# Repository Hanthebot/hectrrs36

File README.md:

# Hectrrs36

sub 100x100 mm 36 key split keyboard with splay - and TRRS jack!

## Specs
Minor derivated work of ezxzeng's [Hector36 keyboard](https://github.com/ezxzeng/hector36), now with RP2040 zero and TRRS!

## Build guide
WIP, but it should be straightforward.
Maybe checkout uploaded images. 

BOM:
- 2 x PCB (reversible)
- 2 x TRRS socket (PJ320A)
- 2 x RP2040 Zero (no pins required, SMD)
- 36 x MX hotswap socket or variants

In case you are going sandwich cases like me:
- 10 x M2 bolt (length 6 mm)
- 10 x M2 nut (diameter 3 mm)
- 10 x M2 standoff (height 7mm - flexible)
- maybe 8-10 bumpons

Tips:
1. Jump at the back
2. Use 90 degree TRRS jack, and 90 degree usb c cable if possible
    -  due to weird locations of TRRS. It may be fixed in the future

With these being said, it could be the most accessible way to try a splayed keyboard / totem layout!

## License
Following the original work, all the work here is licensed under CC BY-NC-SA 4.0.

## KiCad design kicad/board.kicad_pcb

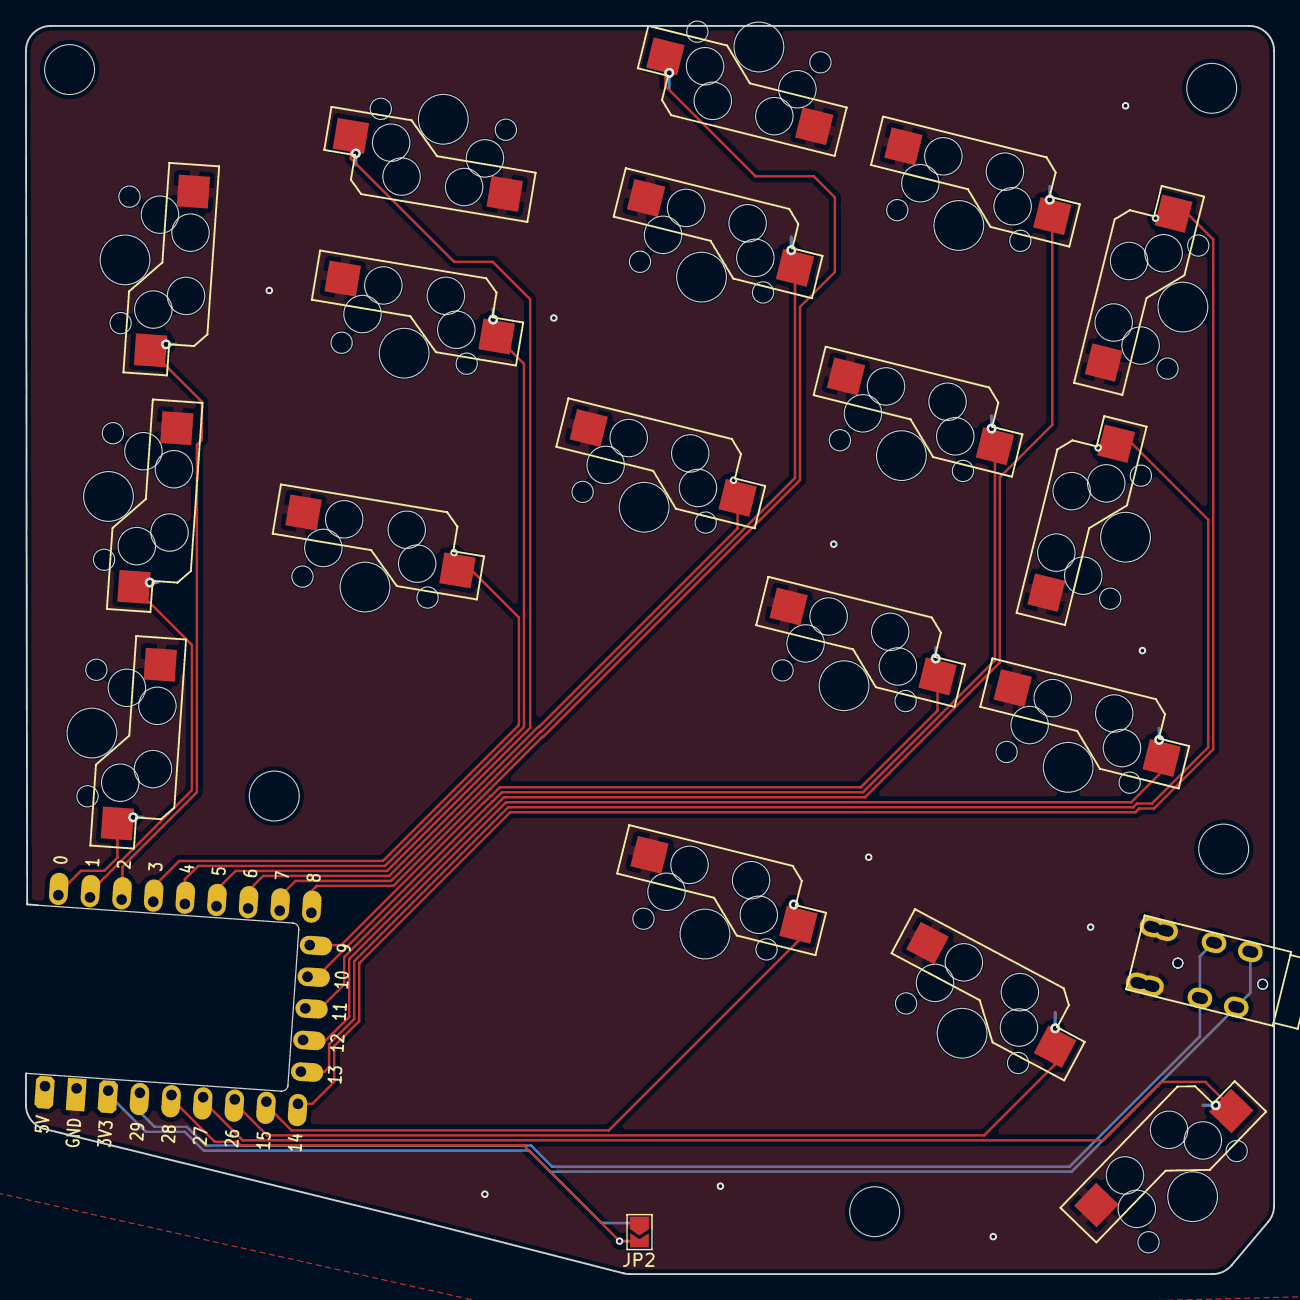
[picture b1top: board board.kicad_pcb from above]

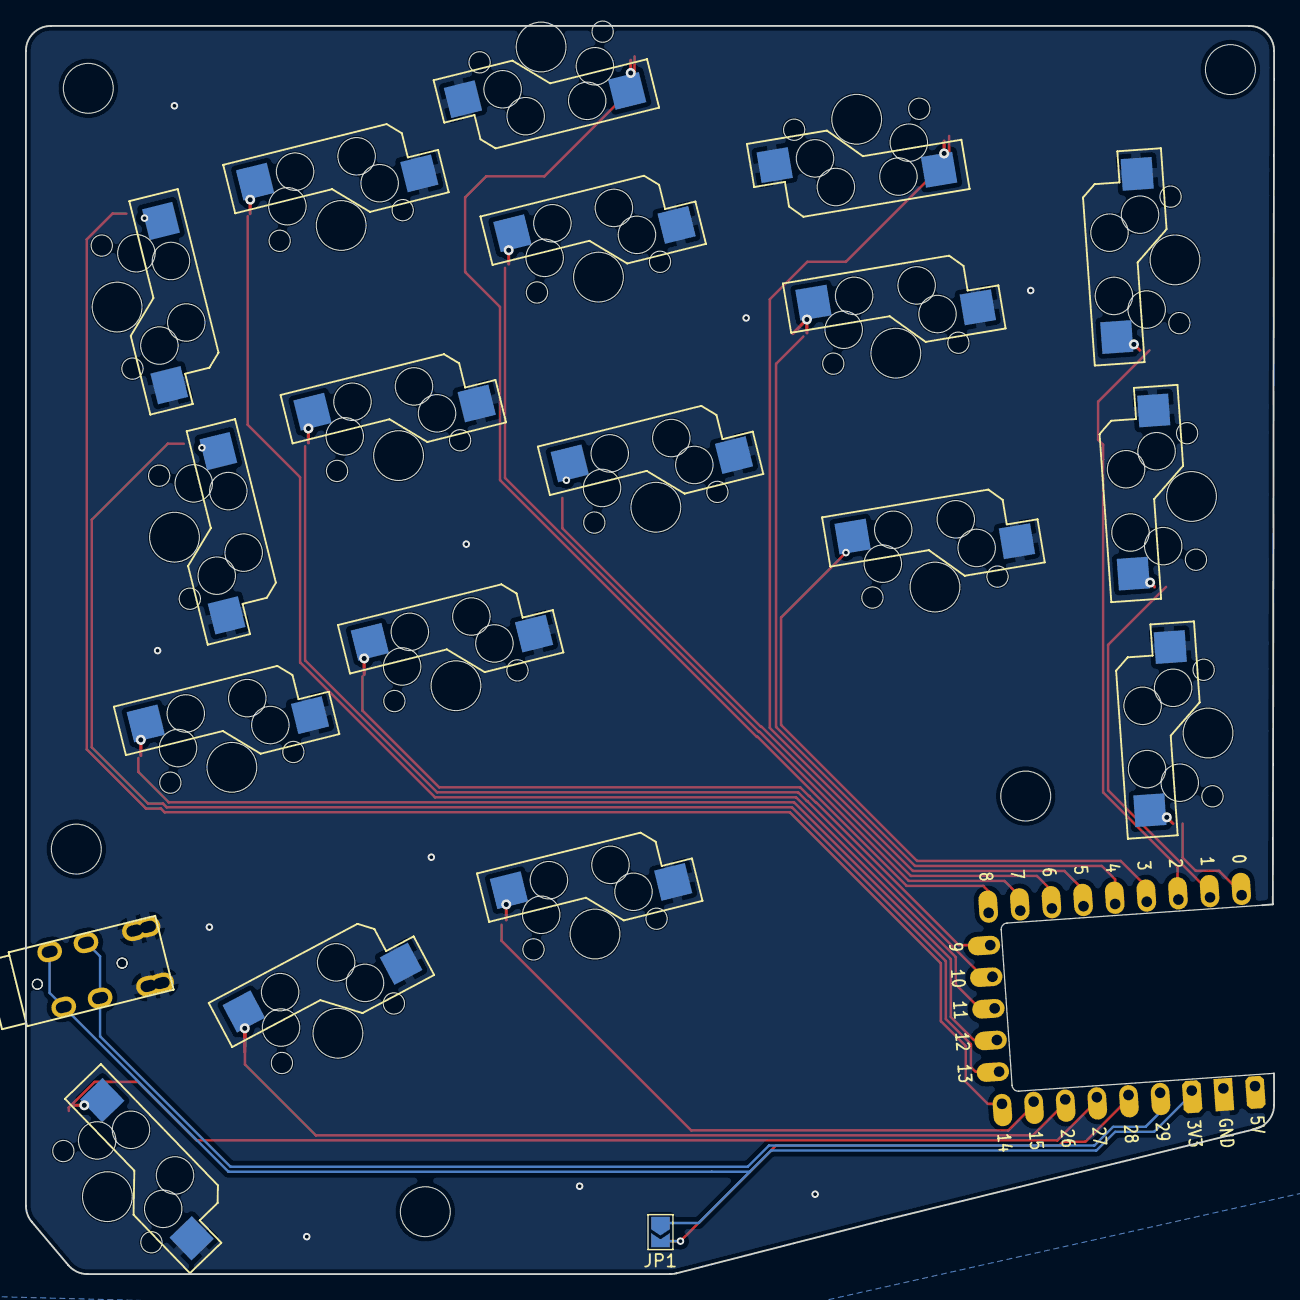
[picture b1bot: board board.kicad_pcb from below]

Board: 2 copper layers, 100.0 x 100.0 mm, 28 parts (2 on the bottom side), 22 nets.

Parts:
AudioJack: TRRS-PJ-320A_PIN
AudioJack#2: TRRS-PJ-320A_PIN
HOLE1, HOLE2, HOLE3, HOLE4, HOLE5: m2 stand cut hole r2
JP1, JP2: SolderJumper_2_Open; SolderJumper-2_P1.3mm_Open_TrianglePad1.0x1.5mm
SW1, SW2, SW3, SW4, SW5, SW6, SW7, SW8, SW9, SW10, SW11, SW12, SW13, SW14, SW15, SW16, SW17, SW18: key-switches
U?: RP2040-Zero-THT-mm

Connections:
GND: AudioJack.S, AudioJack.T, AudioJack#2.S, AudioJack#2.T, JP2.1 (A), SW1.2, SW2.2, SW3.2, SW4.2, SW5.2, SW6.2, SW7.2, SW8.2, SW9.2, SW10.2, SW11.2, SW12.2, SW13.2, SW14.2, SW15.2, SW16.2, SW17.2, SW18.2, U?.31
unnamed: JP1.2 (B), JP2.2 (B), U?.28
SERIAL: AudioJack.R1, AudioJack#2.R1, U?.29
VCC: AudioJack.R2, AudioJack#2.R2, JP1.1 (A), U?.30
matrix_index_bottom: SW10.1, U?.9
matrix_index_home: SW11.1, U?.10
matrix_index_top: SW12.1, U?.11
matrix_inner_bottom: SW13.1, U?.12
matrix_inner_home: SW14.1, U?.13
matrix_inner_top: SW15.1, U?.14
matrix_middle_bottom: SW7.1, U?.6
matrix_middle_home: SW8.1, U?.7
matrix_middle_top: SW9.1, U?.8
matrix_pinky_bottom: SW1.1, U?.0
matrix_pinky_home: SW2.1, U?.1
matrix_pinky_top: SW3.1, U?.2
matrix_ring_bottom: SW4.1, U?.3
matrix_ring_home: SW5.1, U?.4
matrix_ring_top: SW6.1, U?.5
thumb_inner: SW16.1, U?.15
thumb_reachy: SW18.1, U?.27
thumb_tucky: SW17.1, U?.26

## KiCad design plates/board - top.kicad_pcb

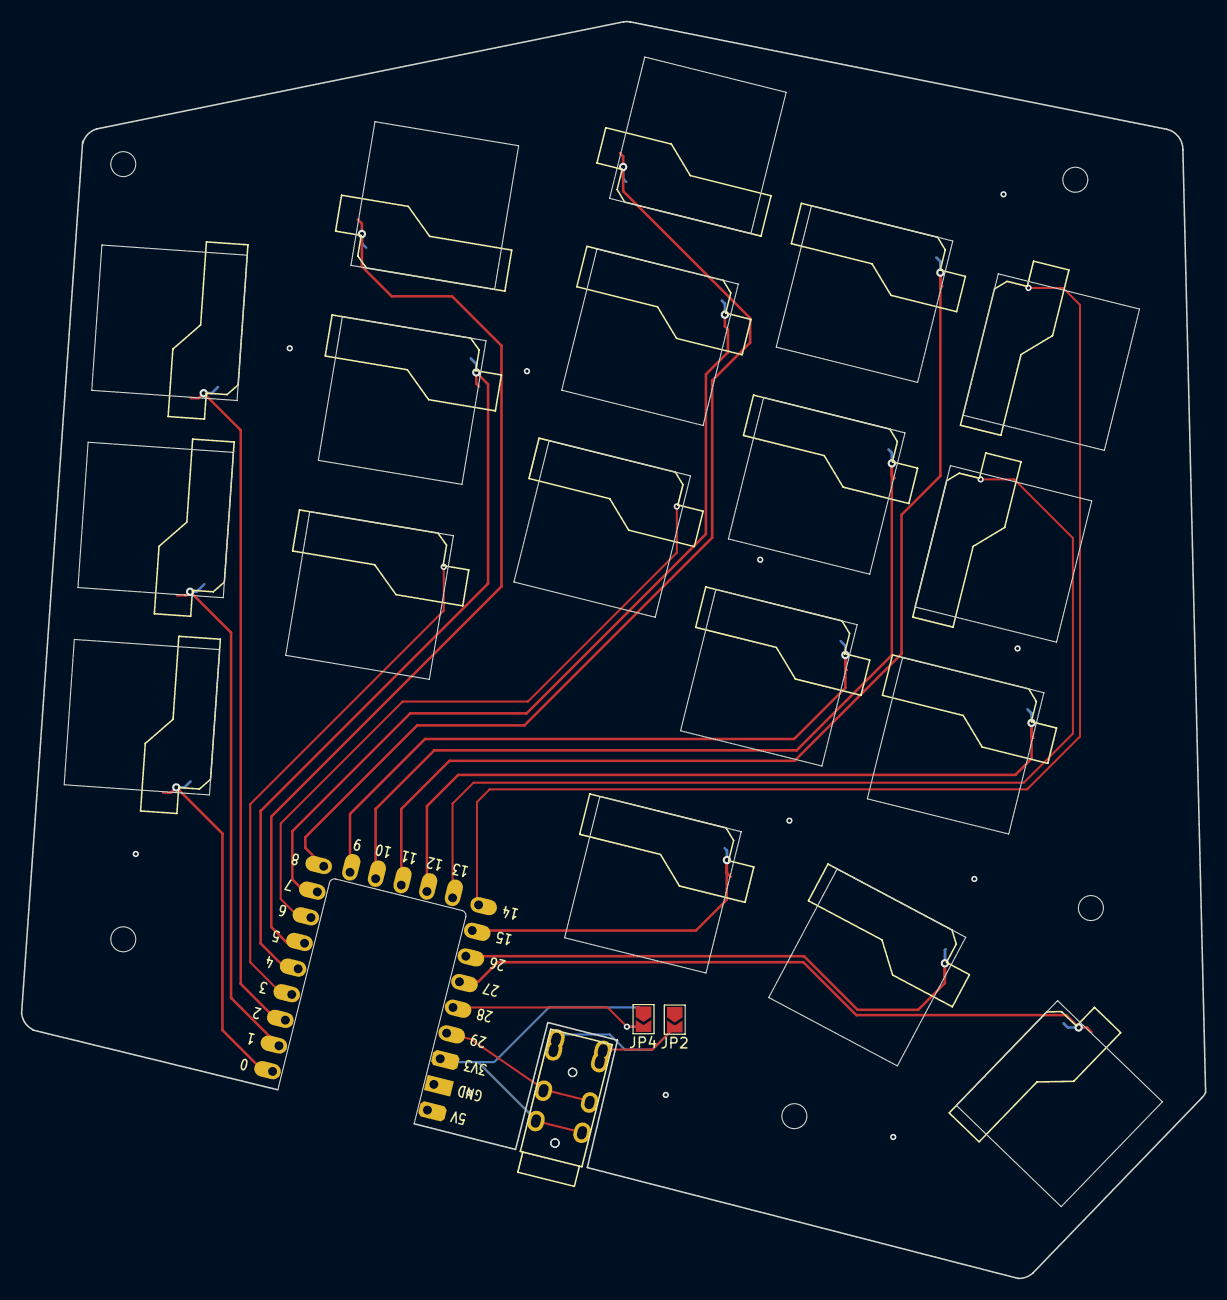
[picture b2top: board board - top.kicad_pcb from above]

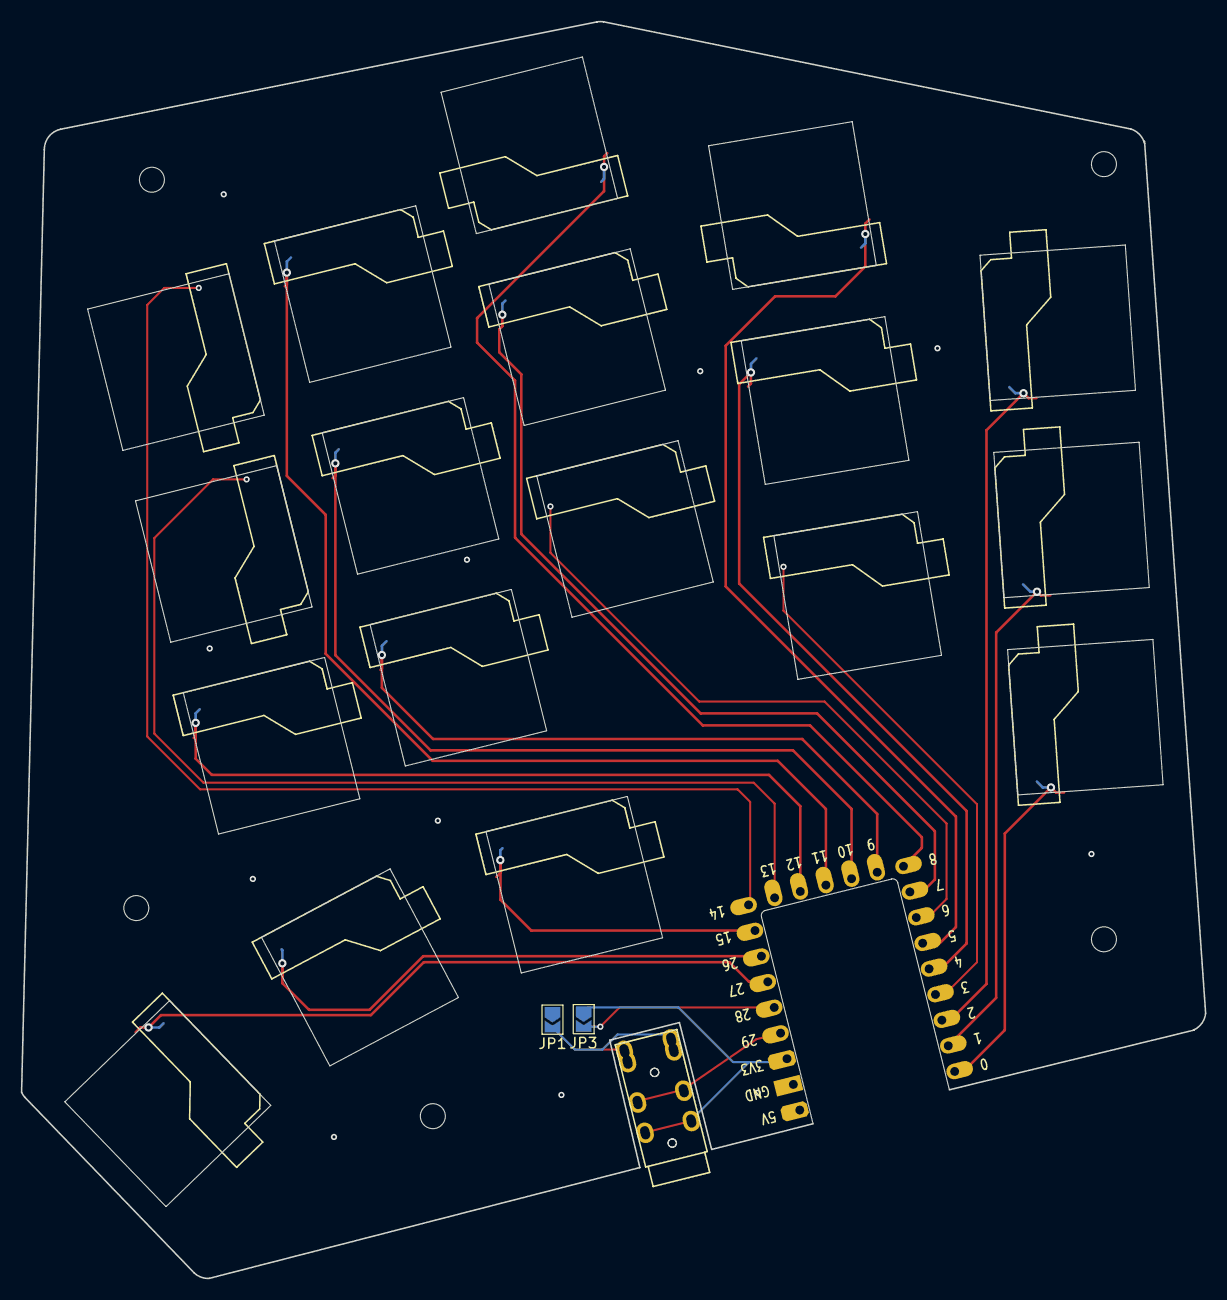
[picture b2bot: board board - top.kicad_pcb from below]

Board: 2 copper layers, 113.8 x 120.8 mm, 30 parts (3 on the bottom side), 6 nets.

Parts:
AudioJack: TRRS-PJ-320A_PIN
AudioJack#2: TRRS-PJ-320A_PIN
HOLE1, HOLE2, HOLE3, HOLE4, HOLE5: hole-m2-screw
JP1, JP2, JP3, JP4: SolderJumper_2_Open; SolderJumper-2_P1.3mm_Open_TrianglePad1.0x1.5mm
SW1, SW2, SW3, SW4, SW5, SW6, SW7, SW8, SW9, SW10, SW11, SW12, SW13, SW14, SW15, SW16, SW17, SW18: hole-switch
U?: RP2040-Zero-THT-mm

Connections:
GND: JP1.1 (A), JP2.1 (A), JP4.1 (A), U?.31
unnamed: AudioJack.T, AudioJack#2.S, JP1.2 (B)
unnamed: AudioJack.S, AudioJack#2.T, JP2.2 (B)
unnamed: JP3.2 (B), JP4.2 (B), U?.28
SERIAL: AudioJack.R1, AudioJack#2.R1, U?.29
VCC: AudioJack.R2, AudioJack#2.R2, JP3.1 (A), U?.30
